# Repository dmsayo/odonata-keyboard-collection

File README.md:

# The Odonata Keyboard Collection

The Odonata design is an ergonomic 4x12, 48 key keyboard powered by QMK in both split and un-split configurations.

## The Lineup
- The Odonata - The original unibody design using Cherry MX switches
- The Odonata-Split - The split variant using Cherry MX switches

## Tools and Services Used
- KiCad for PCB design
- Fusion360 for plate and case design
- JLCPCB for PCB prototyping
- Ponoko for acrylic laser cutting

## Wonderful Resources Used
- [QMK Documentation](https://docs.qmk.fm/#/)
- [Vial QMK Configurator](https://get.vial.today/)
- PCB design articles:
    - [Masterzen's keyboard pcb design blog](https://www.masterzen.fr/2020/05/03/designing-a-keyboard-part-1/) 
    - [ai03's keyboard pcb design tutorial](https://wiki.ai03.com/books/pcb-design/page/pcb-guide-part-1---preparations)

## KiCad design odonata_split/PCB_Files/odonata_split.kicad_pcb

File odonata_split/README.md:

# The Odonata_Split Keyboard

The Odonata_split is an ergonomic 4x6 (x2), 48 key split ergonomic keyboard powered by QMK with Vial support.

## Rationale
Evolving from the original Odonata keyboard, this split variant takes the comfortable yet practical format of the original and allows for a wider range of motion to accomodate for a more ergonomic experience.

## Features

- [x] Allows for socketable Arduino Pro Micros, expanding this keyboards features to include wireless communication, USB-C, etc.
- [x] Fully Programmable using QMK
- [x] Vial supported
- [x] Hotswappable switches with Kailh hotswap sockets
- [x] Compact due to its stacked FR4 sandwich design
- [x] Split halves allow for on-the-fly adjustment for a more ergonomic and comfortable typing experience

## Parts List
- TBD

## Building
- TBD

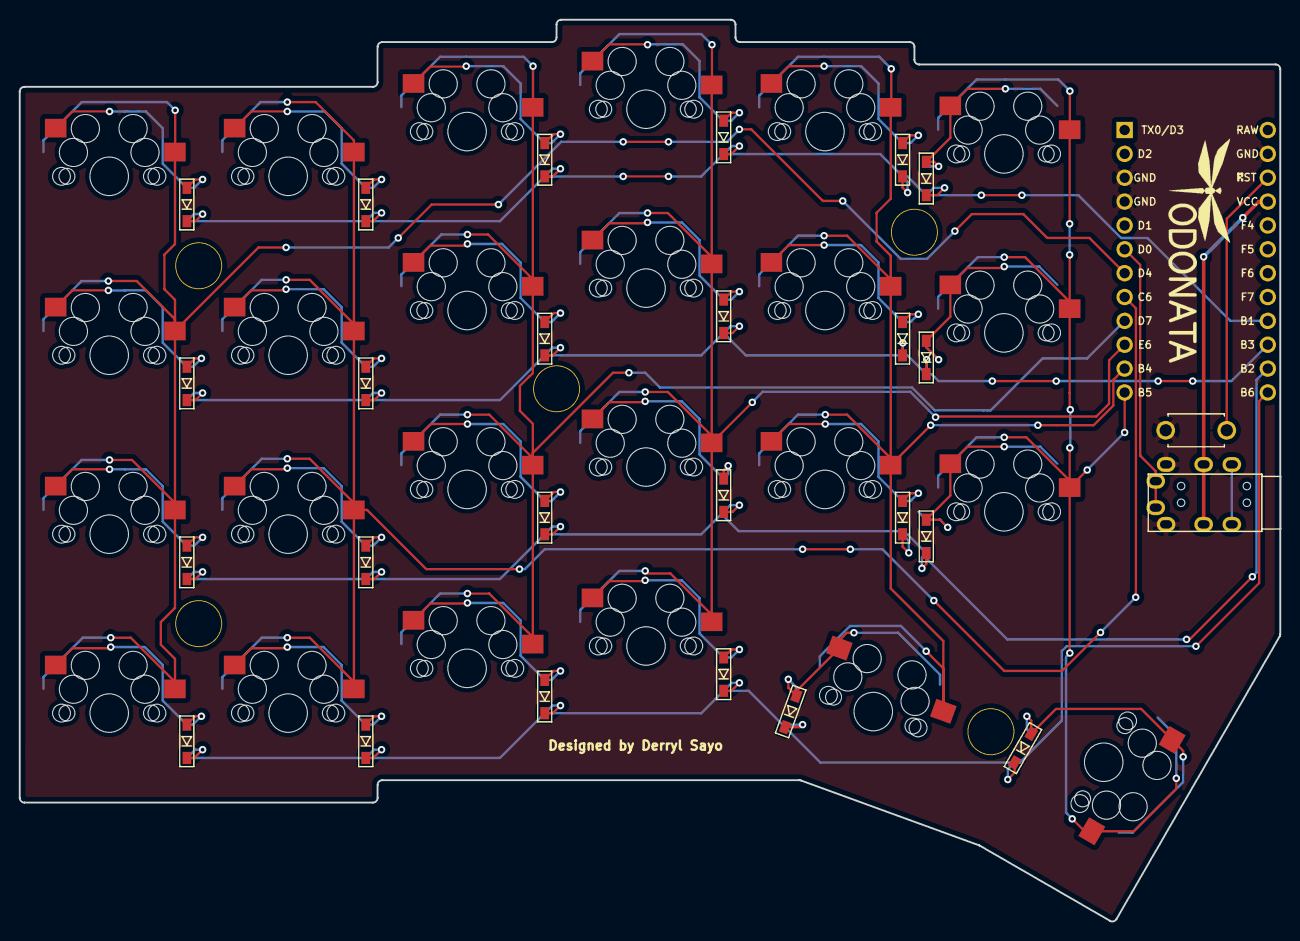
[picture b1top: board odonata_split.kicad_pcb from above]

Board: 2 copper layers, 134.2 x 96.0 mm, 51 parts (0 on the bottom side), 38 nets.

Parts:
D1, D2, D3, D4, D5, D6, D7, D8, D9, D10, D11, D12, D13, D14, D15, D16, D17, D18, D19, D20, D21, D22, D23, D24: D_Small; D3_SMD
J1: trrs_num; TRRS-PJ-320A
K1, K2, K3, K4, K5, K6, K7, K8, K9, K10, K11, K12, K13, K14, K15, K16, K17, K18, K19, K20, K21, K22, K23, K24: KEYSW; CherryMX_MidHeight_Hotswap
SW1: Reset; ResetSW
U1: ProMicro; ArduinoProMicro

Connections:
Col0: K1.1, K7.1, K13.1, K19.1, U1.7
Col1: K2.1, K8.1, K14.1, K20.1, U1.8
Col2: K3.1, K9.1, K15.1, K21.1, U1.9
Col3: K4.1, K10.1, K16.1, K22.1, U1.10
Col4: K5.1, K11.1, K17.1, K23.1, U1.11
Col5: K6.1, K12.1, K18.1, K24.1, U1.12
GND: J1.2, SW1.2, U1.3, U1.4, U1.23
unnamed: D1.2, K1.2
unnamed: D2.2, K2.2
unnamed: D3.2, K3.2
unnamed: D4.2, K4.2
unnamed: D5.2, K5.2
unnamed: D6.2, K6.2
unnamed: D7.2, K7.2
unnamed: D8.2, K8.2
unnamed: D9.2, K9.2
unnamed: D10.2, K10.2
unnamed: D11.2, K11.2
unnamed: D12.2, K12.2
unnamed: D13.2, K13.2
unnamed: D14.2, K14.2
unnamed: D15.2, K15.2
unnamed: D16.2, K16.2
unnamed: D17.2, K17.2
unnamed: D18.2, K18.2
unnamed: D19.2, K19.2
unnamed: D20.2, K20.2
unnamed: D21.2, K21.2
unnamed: D22.2, K22.2
unnamed: D23.2, K23.2
unnamed: D24.2, K24.2
Reset: SW1.1, U1.22
Row0: D1.1, D2.1, D3.1, D4.1, D5.1, D6.1, U1.16
Row1: D7.1, D8.1, D9.1, D10.1, D11.1, D12.1, U1.15
Row2: D13.1, D14.1, D15.1, D16.1, D17.1, D18.1, U1.14
Row3: D19.1, D20.1, D21.1, D22.1, D23.1, D24.1, U1.13
Serial_Pin: J1.1, U1.6
VCC: J1.3, U1.21

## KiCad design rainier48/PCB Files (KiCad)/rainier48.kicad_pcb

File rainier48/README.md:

# The Rainier48 Keyboard

The Rainier48 is an ergonomic 4x12, 48 key ergonomic keyboard powered by QMK.

## Rationale
Having experience typing on both a Planck and a Redox, this keyboard aims to combine the best features of both: the compact size of the Planck and the comfortable thumb cluster of the Redox.

## Features

- [x] USB-C
- [x] Fully Programmable using QMK
- [x] Stacked Acrylic Keyboard Case

## Tools Used
- KiCad for PCB design
- Fusion360 for plate and case design
- JLCPCB for PCB prototyping
- Ponoko for acrylic laser cutting

## Parts List

## Building

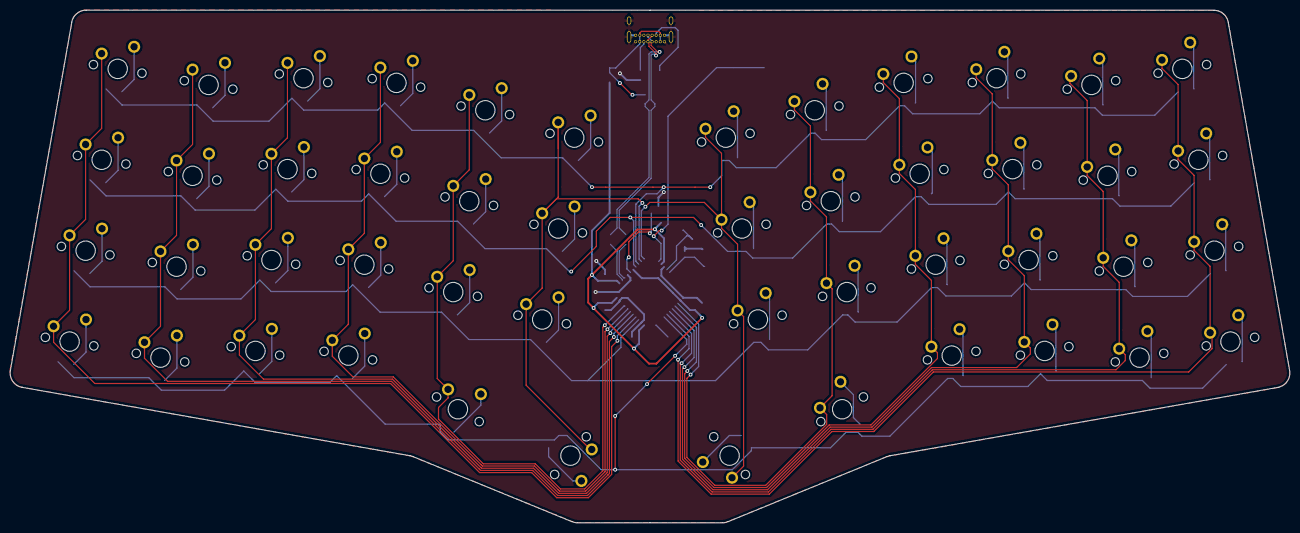
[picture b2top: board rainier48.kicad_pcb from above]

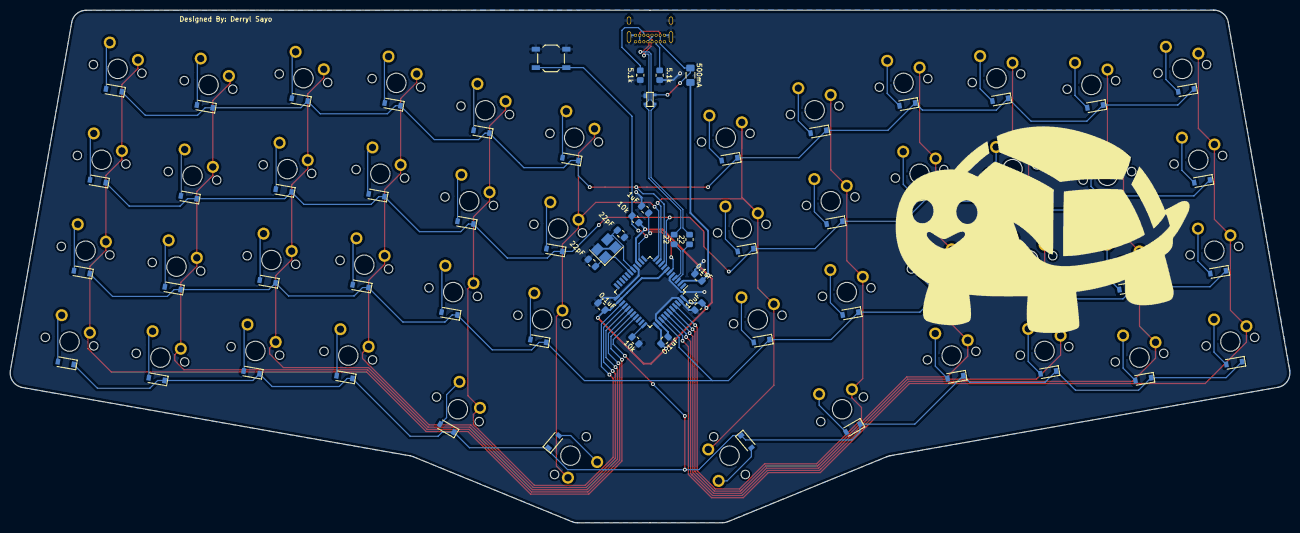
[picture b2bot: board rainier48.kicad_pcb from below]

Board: 2 copper layers, 264.1 x 105.8 mm, 115 parts (67 on the bottom side), 78 nets.

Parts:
C1: 1uF; C_0805_2012Metric_Pad1.18x1.45mm_HandSolder
C2, C3, C4: 0.1uF; C_0805_2012Metric_Pad1.18x1.45mm_HandSolder
C5: 10uF; C_0805_2012Metric_Pad1.18x1.45mm_HandSolder
C6, C7: 22pF; C_0805_2012Metric_Pad1.18x1.45mm_HandSolder
D1, D2, D3, D4, D5, D6, D7, D8, D9, D10, D11, D12, D13, D14, D15, D16, D17, D18, D19, D20, D21, D22, D23, D24, D25, D26, D27, D28, D29, D30, D31, D32, D33, D34, D35, D36, D37, D38, D39, D40, D41, D42, D43, D44, D45, D46, D47, D48: D; D_SOD-123
D49: PRTR5V0U2X; SOT143B
F1: 500mA; Fuse_1206_3216Metric_Pad1.42x1.75mm_HandSolder
J1: USB_C_Receptacle_USB2.0; USB_C_GCT_USB4085
K1, K2, K3, K4, K5, K6, K7, K8, K9, K10, K11, K12, K13, K14, K15, K16, K17, K18, K19, K20, K21, K22, K23, K24, K25, K26, K27, K28, K29, K30, K31, K32, K33, K34, K35, K36, K37, K38, K39, K40, K45, K46, K47, K48: KEYSW; SW_Cherry_MX_PCB_1.00u
K41, K44: KEYSW; SW_Cherry_MX_PCB_1.25u
K42, K43: KEYSW; SW_Cherry_MX_PCB_1.50u
R1, R4: 10k; R_0805_2012Metric_Pad1.20x1.40mm_HandSolder
R2, R3: 22; R_0805_2012Metric_Pad1.20x1.40mm_HandSolder
R5, R6: 5.1k; R_0805_2012Metric_Pad1.20x1.40mm_HandSolder
SW1: SW_PUSH; SW_SPST_TL3342
U1: ATmega32U4-AU; TQFP-44_10x10mm_P0.8mm
Y1: 16MHz; Crystal_SMD_3225-4Pin_3.2x2.5mm_HandSoldering

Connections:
+5V: C2.1, C3.1, C4.1, C5.1, F1.1, R4.1, U1.2, U1.7, U1.14, U1.24, U1.34, U1.44
D+: R3.2, U1.4
D-: R2.2, U1.3
DN: D49.3, J1.A7, J1.B7, R2.1
DP: D49.2, J1.A6, J1.B6, R3.1
GND: C1.2, C2.2, C3.2, C4.2, C5.2, C6.1, C7.2, D49.1, J1.A1, J1.A12, J1.B1, J1.B12, J1.S1, R1.2, R5.2, R6.2, SW1.1, U1.5, U1.15, U1.23, U1.35, U1.43, Y1.2, Y1.4
unnamed: C1.1, U1.6
unnamed: C6.2, U1.17, Y1.1
unnamed: C7.1, U1.16, Y1.3
unnamed: D1.2, K1.2
unnamed: D2.2, K2.2
unnamed: D3.2, K3.2
unnamed: D4.2, K4.2
unnamed: D5.2, K5.2
unnamed: D6.2, K6.2
unnamed: D7.2, K7.2
unnamed: D8.2, K8.2
unnamed: D9.2, K9.2
unnamed: D10.2, K10.2
unnamed: D11.2, K11.2
unnamed: D12.2, K12.2
unnamed: D13.2, K13.2
unnamed: D14.2, K14.2
unnamed: D15.2, K15.2
unnamed: D16.2, K16.2
unnamed: D17.2, K17.2
unnamed: D18.2, K18.2
unnamed: D19.2, K19.2
unnamed: D20.2, K20.2
unnamed: D21.2, K21.2
unnamed: D22.2, K22.2
unnamed: D23.2, K23.2
unnamed: D24.2, K24.2
unnamed: D25.2, K25.2
unnamed: D26.2, K26.2
unnamed: D27.2, K27.2
unnamed: D28.2, K28.2
unnamed: D29.2, K29.2
unnamed: D30.2, K30.2
unnamed: D31.2, K31.2
unnamed: D32.2, K32.2
unnamed: D33.2, K33.2
unnamed: D34.2, K34.2
unnamed: D35.2, K35.2
unnamed: D36.2, K36.2
unnamed: D37.2, K37.2
unnamed: D38.2, K38.2
unnamed: D39.2, K39.2
unnamed: D40.2, K40.2
unnamed: D41.2, K41.2
unnamed: D42.2, K42.2
unnamed: D43.2, K43.2
unnamed: D44.2, K44.2
unnamed: D45.2, K45.2
unnamed: D46.2, K46.2
unnamed: D47.2, K47.2
unnamed: D48.2, K48.2
unnamed: J1.A5, R6.1
unnamed: J1.B5, R5.1
unnamed: R1.1, U1.33
unnamed: R4.2, SW1.2, U1.13
VCC: D49.4, F1.2, J1.A4, J1.A9, J1.B4, J1.B9
col0: K1.1, K13.1, K25.1, K37.1, U1.37
col1: K2.1, K14.1, K26.1, K38.1, U1.38
col2: K3.1, K15.1, K27.1, K39.1, U1.39
col3: K4.1, K16.1, K28.1, K40.1, U1.40
col4: K5.1, K17.1, K29.1, K41.1, U1.41
col5: K6.1, K18.1, K30.1, K42.1, U1.10
col6: K7.1, K19.1, K31.1, K43.1, U1.11
col7: K8.1, K20.1, K32.1, K44.1, U1.25
col8: K9.1, K21.1, K33.1, K45.1, U1.26
col9: K10.1, K22.1, K34.1, K46.1, U1.27
col10: K11.1, K23.1, K35.1, K47.1, U1.28
col11: K12.1, K24.1, K36.1, K48.1, U1.29
row0: D1.1, D2.1, D3.1, D4.1, D5.1, D6.1, D7.1, D8.1, D9.1, D10.1, D11.1, D12.1, U1.9
row1: D13.1, D14.1, D15.1, D16.1, D17.1, D18.1, D19.1, D20.1, D21.1, D22.1, D23.1, D24.1, U1.8
row2: D25.1, D26.1, D27.1, D28.1, D29.1, D30.1, D31.1, D32.1, D33.1, D34.1, D35.1, D36.1, U1.36
row3: D37.1, D38.1, D39.1, D40.1, D41.1, D42.1, D43.1, D44.1, D45.1, D46.1, D47.1, D48.1, U1.30

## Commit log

2022-01-18 refactored file structure
2022-01-18 added .gitignore
2022-01-18 added to gitignore
2022-01-18 .gitignore not working
2022-01-18 Added information to readme
2022-03-08 added keymap pdf and split firmware files
2022-03-08 edited default split keymap readme
2022-04-26 begin naming refactor
2022-04-26 added odonata firmware
2022-04-26 updated readmes
2022-04-26 fixed vial unlock combo
2022-04-28 fixed odonata mouse keys
